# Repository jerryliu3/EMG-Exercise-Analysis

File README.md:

# EMG-Exercise-Analysis

## Overview:

* Circuits and PCB for 4 channel EMG data acquisition
* Bluno beetle and Android app interfacing for wireless real-time transfer of data
* Machine learning and implemention of Random Forest Classifier for 9 exercises

## Current Project Functionalities:

1. Take EMG signals from 4 channels and pass them through the PCB to remove noise and amplify the signal

2. Transfer the data over Bluetooth to the Android app which receives and updates multiline graphs in real time.

3. Save the data on a local file or online database

4. Put the data through a random forest classifier for exercise classification of 9 different exercises

## Problems We Encountered:

* Low quality circuit boards are near impossible to work with
* Natural inconsistencies in the hardware leading to hours of debugging
* Lack of guides for using a multiplexer
* Training the random forest classifier

## To Do:

1. Attach the “nervous system” to the “skin”

2. Pass data through seglearn
	* Option 1: get seglearn working on a phone
	* Option 2: get the data off the phone and run seglearn on a computer

3. Improve machine learning and database handling

4. Test interfacing of the app and the Bluno Beetle instead of the app and Arduino for communication

## Maintainers:

* [Andrew Luo](https://github.com/Andrew-Luo1)
* [Earvin Tio](https://github.com/EarvinTio)
* [Jerry Liu](https://github.com/jerryliu3)

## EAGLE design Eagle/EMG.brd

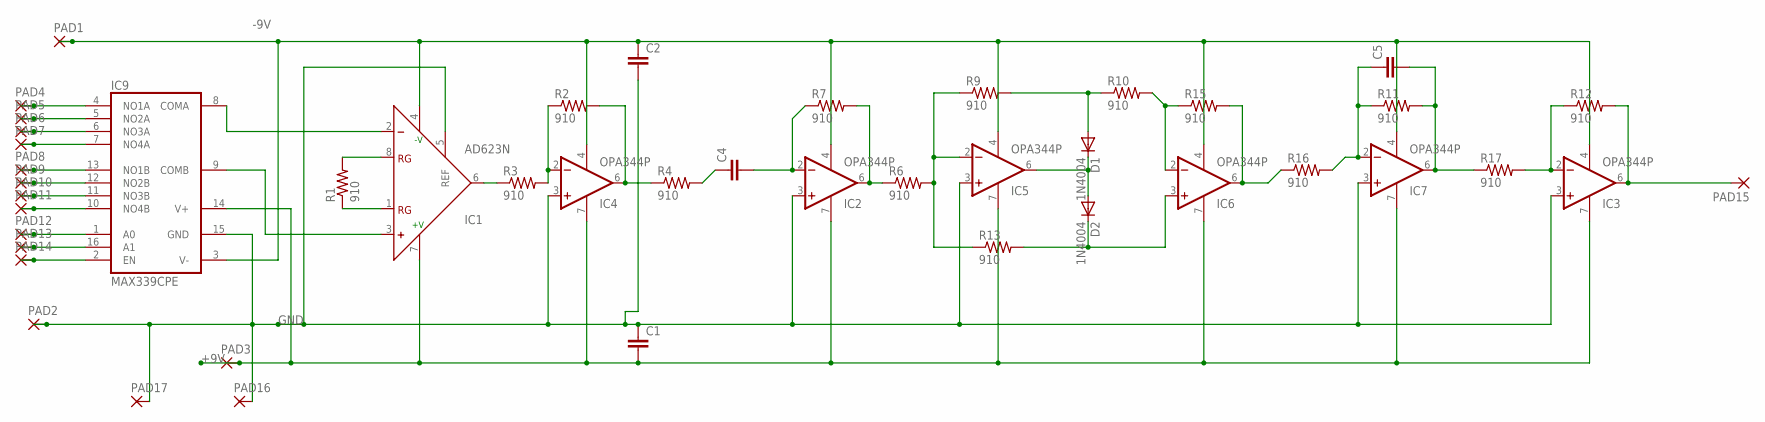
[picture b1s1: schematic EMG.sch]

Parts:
C1, C2, C4, C5: C2,5-3; C2.5-3
D1, D2: 1N4004; DO41-10
IC1: AD623N; DIL08
IC2, IC3, IC4, IC5, IC6, IC7: OPA344P; DIL08
IC9: MAX339CPE; DIL16
PAD1, PAD2, PAD3, PAD4, PAD5, PAD6, PAD7, PAD8, PAD9, PAD10, PAD11, PAD12, PAD13, PAD14, PAD15, PAD16, PAD17: 2,15/1,0
R1, R2, R3, R4, R6, R7, R9, R10, R11, R12, R13, R15, R16, R17: 910; 0204/7

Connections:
+9V: C1.2, IC1.7 (+V), IC2.7 (V+), IC3.7 (V+), IC4.7 (V+), IC5.7 (V+), IC6.7 (V+), IC7.7 (V+), IC9.14 (V+), PAD3.1
-9V: C2.1, IC1.4 (-V), IC2.4 (V-), IC3.4 (V-), IC4.4 (V-), IC5.4 (V-), IC6.4 (V-), IC7.4 (V-), IC9.3 (V-), PAD1.1
GND: C1.1, C2.2, IC1.5 (REF), IC2.3 (+IN), IC3.3 (+IN), IC4.3 (+IN), IC5.3 (+IN), IC7.3 (+IN), IC9.15 (GND), PAD2.1, PAD16.1, PAD17.1
unnamed: IC1.8 (RG), R1.2
unnamed: IC1.1 (RG), R1.1
unnamed: IC1.6 (OUT), R3.1
unnamed: IC4.2 (-IN), R2.1, R3.2
unnamed: IC4.6 (OUT), R2.2, R4.1
unnamed: C4.1, R4.2
unnamed: C4.2, IC2.2 (-IN), R7.1
unnamed: IC5.2 (-IN), R6.2, R9.1, R13.1
unnamed: D1.A, R9.2, R10.1
unnamed: IC2.6 (OUT), R6.1, R7.2
unnamed: IC6.6 (OUT), R15.2, R16.1
unnamed: C5.1, IC7.2 (-IN), R11.1, R16.2
unnamed: C5.2, IC7.6 (OUT), R11.2, R17.1
unnamed: IC3.2 (-IN), R12.1, R17.2
unnamed: IC3.6 (OUT), PAD15.1, R12.2
unnamed: D2.C, IC6.3 (+IN), R13.2
unnamed: D1.C, D2.A, IC5.6 (OUT)
unnamed: IC6.2 (-IN), R10.2, R15.1
unnamed: IC1.2 (-), IC9.8 (COMA)
unnamed: IC1.3 (+), IC9.9 (COMB)
unnamed: IC9.10 (NO4B), PAD11.1
unnamed: IC9.4 (NO1A), PAD4.1
unnamed: IC9.5 (NO2A), PAD5.1
unnamed: IC9.6 (NO3A), PAD6.1
unnamed: IC9.7 (NO4A), PAD7.1
unnamed: IC9.13 (NO1B), PAD8.1
unnamed: IC9.11 (NO3B), PAD10.1
unnamed: IC9.12 (NO2B), PAD9.1
unnamed: IC9.1 (A0), PAD12.1
unnamed: IC9.16 (A1), PAD13.1
unnamed: IC9.2 (EN), PAD14.1

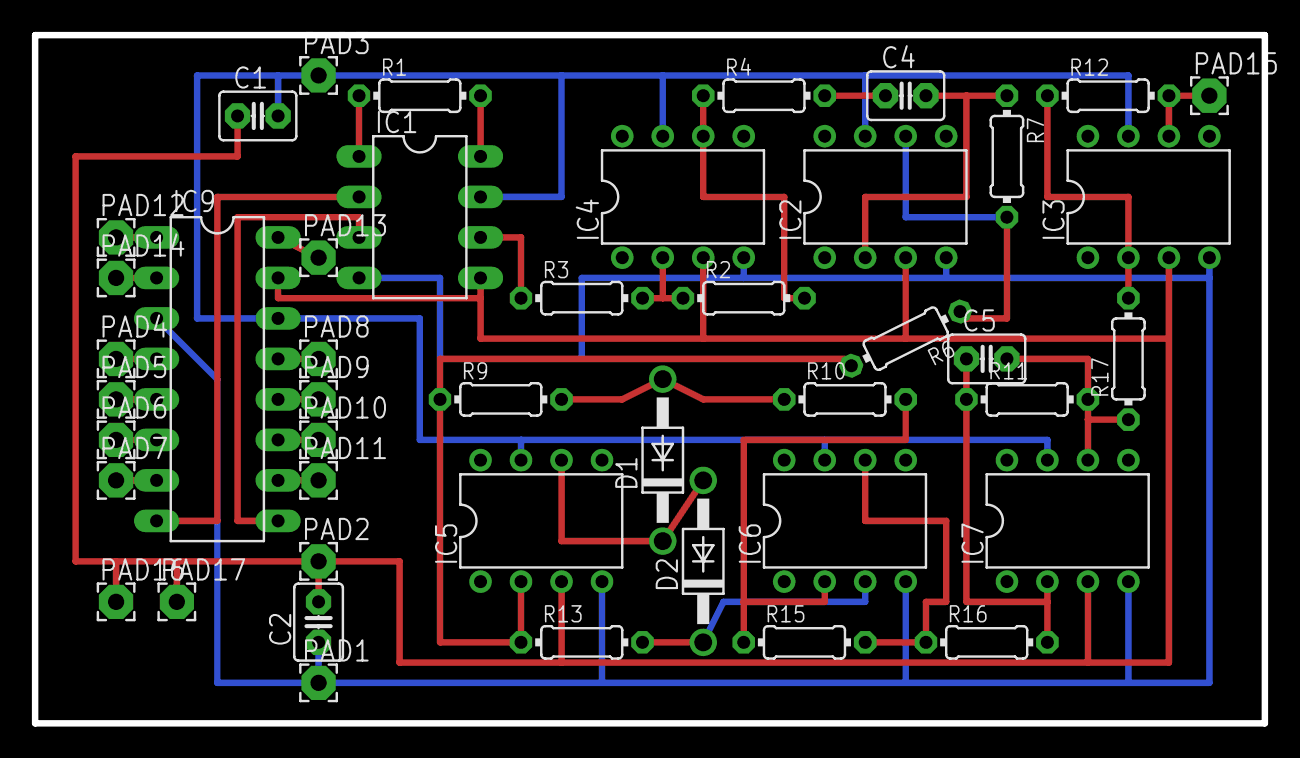
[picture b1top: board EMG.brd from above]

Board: 2 copper layers, 77.1 x 43.2 mm, 45 parts (0 on the bottom side), 34 nets.

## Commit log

2018-02-15 Arduino code for 4 channel EMG multiplexor selection
2018-02-15 Add Andrew's code that he was too irresponsible to add himself
2018-02-26 Add PCB schematic
2018-02-26 Added mux code for hacked mux
2018-02-27 Add final mux code (partially working)
2018-02-27 Add mux screenshot
2018-03-02 Working MUX code that plots 4 channels live
2018-03-04 All features, will implement classification
2018-03-04 Add single file version of code
2018-03-16 Implement seglearn on UCI data -Earvin
2018-03-23 new mux
2018-03-23 Added data
2018-03-29 Segment back pulldown exercise
2018-03-30 Explored seglearn with our own collected data
2018-04-04 Add basic transistor code
2018-04-05 Reorganizing
2018-04-05 Add mux datasheet
2018-04-05 Add IA datasheet
2018-04-05 Add Earvin's IA datasheet
2018-04-05 Add op amp datasheet
2018-04-06 Fix hole connections
2018-04-06 Add transistor datasheet
2018-04-07 Fixing Jerry's upload
2018-04-07 Test adding phone app code
2018-04-07 Add initial beetle code
2018-04-07 Design Rule Check
2018-04-07 Compressed brd
2018-04-08 Upload 1 by 1 send code
2018-04-08 Add accelerometer real time graph
2018-04-08 Complete real time accelerometer graph
2018-04-08 Add graphing to TestActivity
2018-04-08 Add android app code with graphing
2018-04-09 Remove bad app and add working one
2018-04-09 renamed transistor datasheet
2018-04-10 Add multichannel plotting file
2018-04-12 Fix bugs and tested full workflow
2018-04-12 Jerry messed up
2018-04-13 data collection
2018-04-17 ran new data through seglearn pipeline
2018-04-19 Properly divided data
2018-04-19 Add matlab code for parsing data csvs together - Jerry
2018-04-20 add new data
2018-04-20 Python code to rewrite the data we collect into the proper format
2018-04-20 reformatted data
2018-04-20 Improve compile data program and upload concatenated data
2018-04-27 most recent version that runs on most recent collected data
2018-05-08 using the Bluno now
